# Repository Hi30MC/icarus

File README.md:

# icarus
Files pertaining to the development of my personal custom keyboard Icarus.

# Ergogen
The keyboard and pcb layout were generated using Ergogen locally. The config files and corresponding outputs can be found in the `ergogen` folder. There are custom footprints that generate 3d models on the footprints of all components, and these are found in `final_pcbs/components`. **The path for these are custom to my file setup, and thus will most likely not work on your machine. Please change the corresponding file paths if you wish to locally build this model.**

# KiCad
The corresponding PCB outputs from Ergogen were traced in KiCad. The final traced PCBs, along with exported STEP files are found in the `final_pcbs` folder. Currently, **the final PCBs do not have the switch and keycap models on the footprints of the switches, and there are traces which have been shown to be on fragile board sections.** Both of these changes will be updated in the near future and this notice will be removed once that happens.

# Case files
The case files were constructed in Onshape. One can view these files [here](https://cad.onshape.com/documents/795d5125a76cdfb5a48cf88b/w/a7573c951f90309017d525a7/e/47b874ca74b5b2133d47f936). There are also STEP files in this repo, in the `case_files` folder. Note that the case files provided are for the left side of the keyboard only, and the right side is simply a mirror image of the left side.

## Travel case files

As of 01 July '26, there are travel case files in the works. Please stay tuned for their release. 

# ZMK configuration.

Icarus currently runs ZMK. The configuration repository and current firmware can be found [here](https://github.com/Hi30MC/zmk-config).

# Physical build notes

This case was designed and printed for FDM, though the battery cage is a major flaw in the design. There are supports that are best printed as "normal slim" supports on Orca, for example, as these had the cleanest release. I found that it was best to print the ports/switches/etc on the case as-is, then clean up with a file, though one may find success with adding supports and removing those manually. Additionally, I reccomend placing brim ears on all corners of the faceplate/skirt print, as well as the baseplate as they tend to warp during printing. Mounting the baseplate to the PCB was done with M2.5 self-threading screws, which need washers to secure onto the board. **Print these separately, and not attached to the baseplate.** There is also a known issue with the right PCB's battery jack hitting against the Kailh hotswap bracket, which will be fixed soon™. Finally, to ensure that the keys fit into the shield, one must use flush cutters on the key-side of the shield to cut the soldering joints flush. It doesn't need to be perfectly flush, but as flush as possible is best. If any other issues arise in whoever decides to build this, please reach out!

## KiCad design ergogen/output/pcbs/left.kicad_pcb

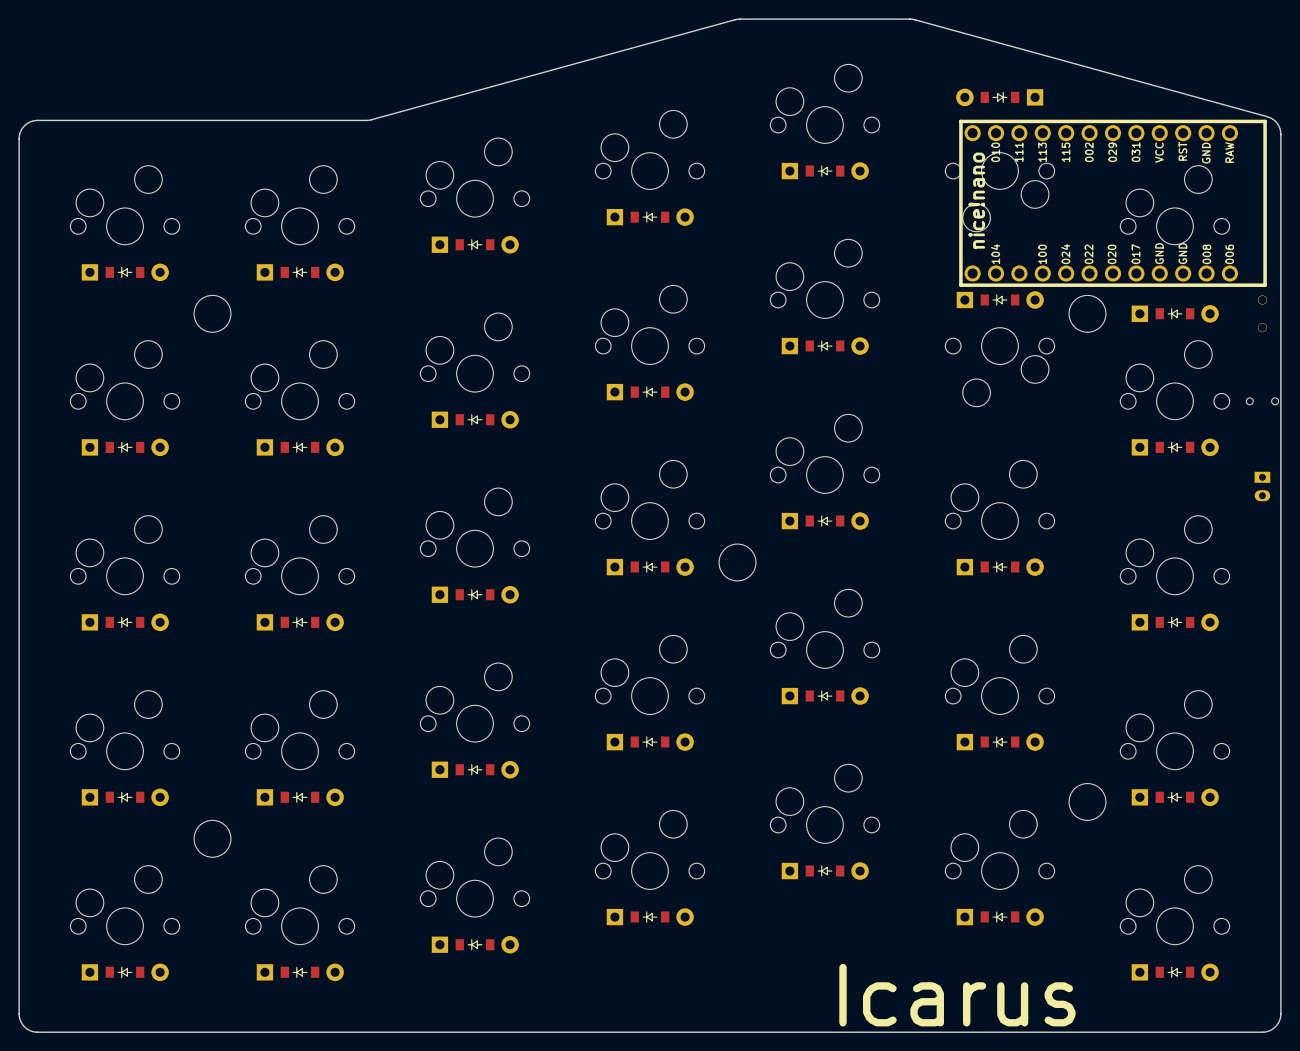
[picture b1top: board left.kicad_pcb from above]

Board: 2 copper layers, 137.0 x 110.0 mm, 74 parts (0 on the bottom side), 51 nets, no tracks yet.

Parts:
B1: Panasonic_EVQPUL_EVQPUC
D1, D2, D3, D4, D5, D6, D7, D8, D9, D10, D11, D12, D13, D14, D15, D16, D17, D18, D19, D20, D21, D22, D23, D24, D25, D26, D27, D28, D29, D30, D31, D32, D33, D34, D35: ComboDiode
JST1: JST_PH_S2B-PH-K_02x2.00mm_Angled
MCU1: nice_nano
S1, S2, S3, S4, S5, S6, S7, S8, S9, S10, S11, S12, S13, S14, S15, S16, S17, S18, S19, S20, S21, S22, S23, S24, S25, S26, S27, S28, S29, S30, S31, S32, S33, S34, S35: MX
T1: SPDT_C128955

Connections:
GND: B1.1, JST1.2, MCU1.3, MCU1.4, MCU1.23
P002: MCU1.18, S1.1, S2.1, S3.1, S4.1, S5.1
P009: MCU1.13, S26.1, S27.1, S28.1, S34.1, S35.1
P010: MCU1.14, S21.1, S22.1, S23.1, S24.1, S25.1
P017: D5.1, D10.1, D15.1, D20.1, D25.1, D34.1, D35.1, MCU1.5
P020: D1.1, D6.1, D11.1, D16.1, D21.1, D26.1, D29.1, MCU1.6
P022: D2.1, D7.1, D12.1, D17.1, D22.1, D27.1, D30.1, MCU1.7
P024: D3.1, D8.1, D13.1, D18.1, D23.1, D28.1, D31.1, MCU1.8
P031: MCU1.20, S29.1, S30.1, S31.1, S32.1, S33.1
P100: D4.1, D9.1, D14.1, D19.1, D24.1, D32.1, D33.1, MCU1.9
P111: MCU1.15, S16.1, S17.1, S18.1, S19.1, S20.1
P113: MCU1.16, S11.1, S12.1, S13.1, S14.1, S15.1
P115: MCU1.17, S6.1, S7.1, S8.1, S9.1, S10.1
RAW: MCU1.24, T1.2
RST: B1.2, MCU1.22
index_bottom: D27.2, S27.2
index_home: D28.2, S28.2
index_num: D34.2, S35.2
index_space: D26.2, S26.2
index_top: D33.2, S34.2
inner_bottom: D30.2, S30.2
inner_home: D31.2, S31.2
inner_num: D35.2, S33.2
inner_space: D29.2, S29.2
inner_top: D32.2, S32.2
macro_bottom: D2.2, S2.2
macro_home: D3.2, S3.2
macro_num: D5.2, S5.2
macro_space: D1.2, S1.2
macro_top: D4.2, S4.2
middle_bottom: D22.2, S22.2
middle_home: D23.2, S23.2
middle_num: D25.2, S25.2
middle_space: D21.2, S21.2
middle_top: D24.2, S24.2
outer_bottom: D7.2, S7.2
outer_home: D8.2, S8.2
outer_num: D10.2, S10.2
outer_space: D6.2, S6.2
outer_top: D9.2, S9.2
pinky_bottom: D12.2, S12.2
pinky_home: D13.2, S13.2
pinky_num: D15.2, S15.2
pinky_space: D11.2, S11.2
pinky_top: D14.2, S14.2
pos: JST1.1, T1.1
ring_bottom: D17.2, S17.2
ring_home: D18.2, S18.2
ring_num: D20.2, S20.2
ring_space: D16.2, S16.2
ring_top: D19.2, S19.2

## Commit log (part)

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2026-04-29 base commit with some test files
2026-04-29 TO-DO: aux bits on the PCB (battery, reset, and on/off)
2026-04-29 right board
2026-04-30 basically done pcbs
2026-04-30 pcbs without images
2026-04-30 change license
2026-04-30 remove .history
2026-05-19 redesign for short board, left but no right pcb. Final pcbs for old design
2026-05-19 restructured file system; final short pcbs. Old PCBs are trashed and other cleaning.
2026-06-05 regenned with board flipped correctly; traced pcbs to be redone
2026-06-05 reorganised files, board retrace todo
2026-06-05 regen board with custom footprints to have 3d models autogenned
2026-06-09 all board retraced and finalised; ordered.
2026-06-10 change README, add .step for right_pcb
2026-06-16 Add ZMK configuration information to README
    Added ZMK configuration section with links to the repository and firmware.
2026-06-23 final case files
